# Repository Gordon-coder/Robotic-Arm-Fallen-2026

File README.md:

# Robotic Arm

This is the github repo for the Robotic Arm Project in Hack Club's Fallen 2026.

# Hardware

We have decided to make seperate pcbs for the different parts of the robotic arm to increaase modularity and speed up development. the modules are connected either through a uart line or the ESP-NOW protocol.

PCB for the main arm

Schematic for the main arm

schematic for the camera

# Team Members

<ul>
    <li>
        Gordon Peng
    </li>
    <li>
        Manvith
    </li>
    <li>
        Sarthak Vishwakarma
    </li>
</ul>

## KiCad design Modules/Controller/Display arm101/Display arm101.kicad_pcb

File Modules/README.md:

# Module Development Notes

The mount has 4 4mm holes in a circle with radius 10mm. All modules mounted on the claw mount must use the exact same mounting point.

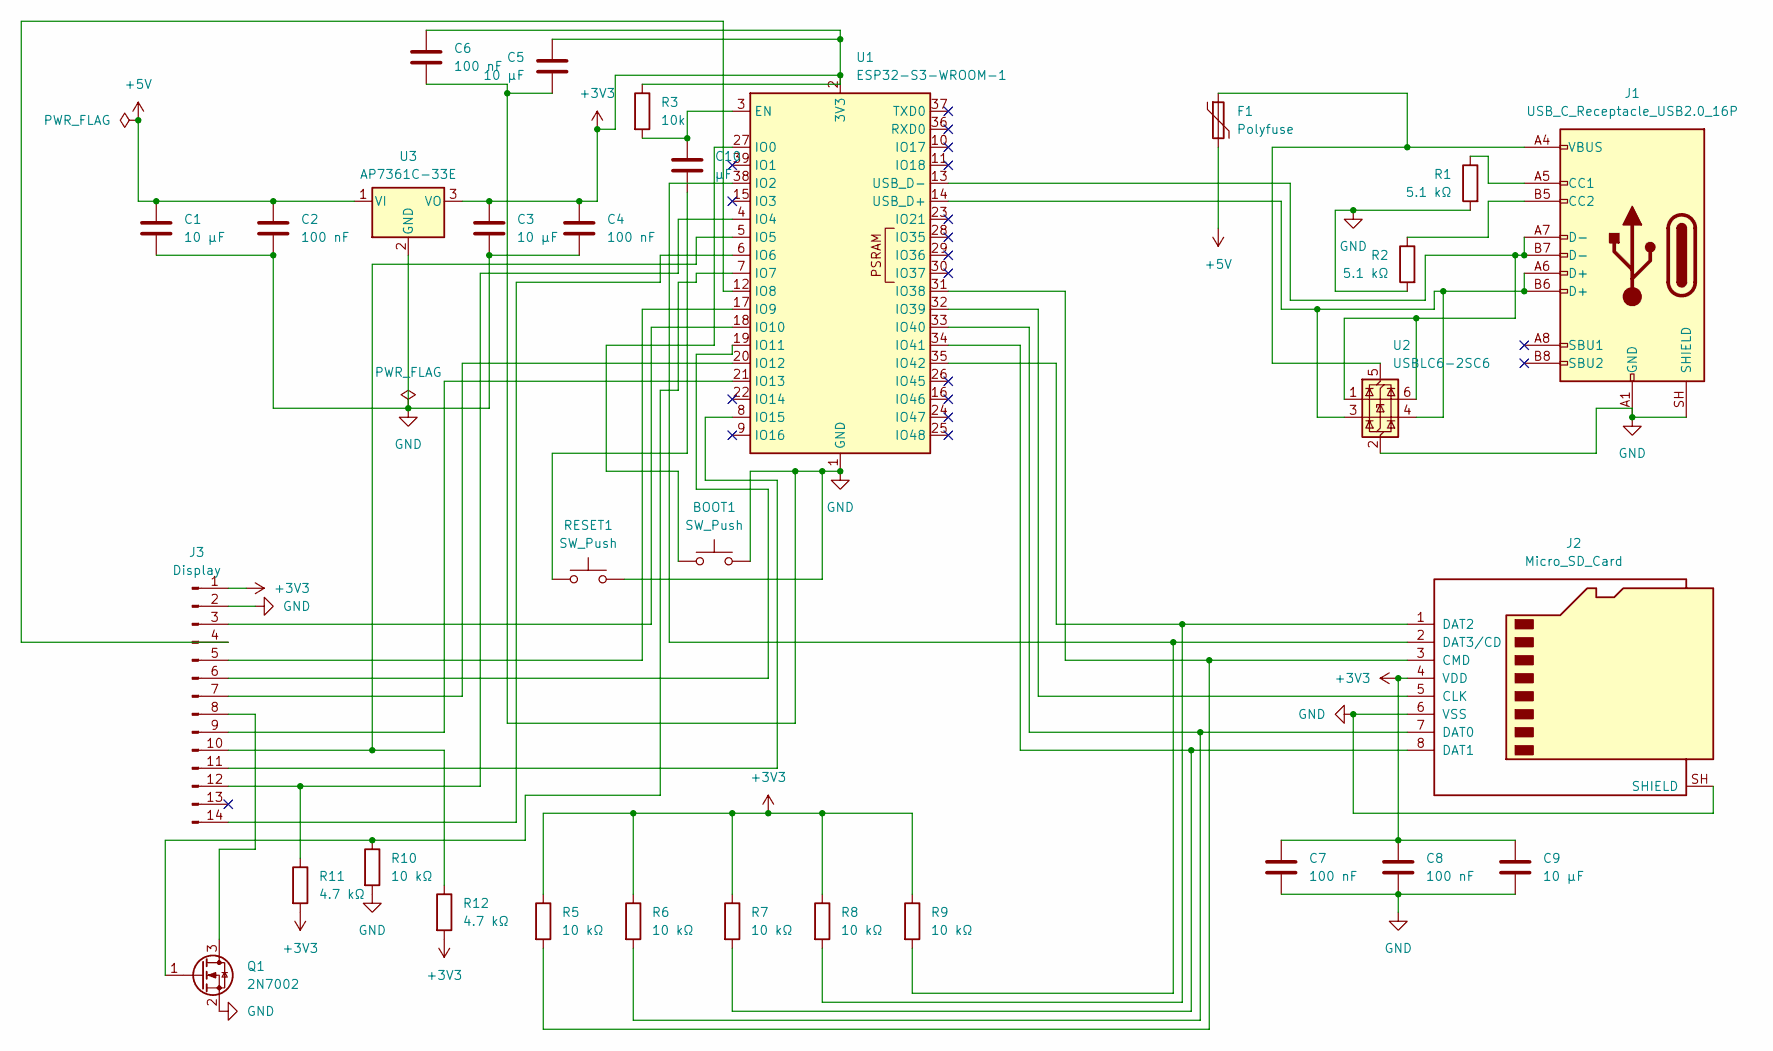
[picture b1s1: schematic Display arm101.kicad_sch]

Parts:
BOOT1: SW_Push; SW_PUSH_6mm
C1, C3, C5, C9: 10 µF; C_0805_2012Metric
C2, C4, C6, C7, C8: 100 nF; C_0805_2012Metric
C10: µF; C_0805_2012Metric
F1: Polyfuse; Fuse_1206_3216Metric
J1: USB_C_Receptacle_USB2.0_16P; USB_C_Receptacle_HRO_TYPE-C-31-M-12
J2: Micro_SD_Card; microSD_HC_Hirose_DM3AT-SF-PEJM5
J3: Display; PinSocket_1x14_P2.54mm_Vertical
Q1: 2N7002; SOT-23
R1, R2: 5.1 kΩ; R_0805_2012Metric
R3: 10k; R_0805_2012Metric
R5, R6, R7, R8, R9, R10: 10 kΩ; R_0805_2012Metric
R11, R12: 4.7 kΩ; R_0805_2012Metric
RESET1: SW_Push; SW_SPST_TL3342
U1: ESP32-S3-WROOM-1
U2: USBLC6-2SC6; SOT-23-6
U3: AP7361C-33E; SOT-223-3_TabPin2

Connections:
+3V3: C3.1, C4.1, C5.1, C6.1, C7.1, C8.1, C9.1, J2.4 (VDD), J3.1, R3.1, R5.1, R6.1, R7.1, R8.1, R9.1, R11.2, R12.2, U1.2 (3V3), U3.3 (VO)
+5V: C1.1, C2.1, F1.2, U3.1 (VI)
GND: BOOT1.2, C1.2, C2.2, C3.2, C4.2, C5.2, C6.2, C7.2, C8.2, C9.2, J1.A1 (GND), J1.A12 (GND), J1.B1 (GND), J1.B12 (GND), J1.SH (SHIELD), J2.6 (VSS), J2.SH (SHIELD), J3.2, Q1.2 (S), R1.2, R2.2, R10.2, RESET1.2, U1.1 (GND), U1.40 (GND), U1.41 (GND), U2.2 (GND), U3.2 (GND)
unnamed: C10.2, RESET1.1
unnamed: J1.A5 (CC1), R1.1
unnamed: J1.B5 (CC2), R2.1
unnamed: J2.5 (CLK), U1.32 (IO39)
unnamed: J2.3 (CMD), R5.2, U1.31 (IO38)
unnamed: J2.7 (DAT0), R6.2, U1.33 (IO40)
unnamed: J2.8 (DAT1), R7.2, U1.34 (IO41)
unnamed: J2.1 (DAT2), R8.2, U1.35 (IO42)
unnamed: J2.2 (DAT3/CD), R9.2, U1.38 (IO2)
unnamed: J3.3, U1.18 (IO10)
unnamed: J3.4, U1.12 (IO8)
unnamed: J3.5, U1.17 (IO9)
unnamed: J3.6, U1.19 (IO11)
unnamed: J3.7, U1.20 (IO12)
unnamed: J3.8, Q1.3 (D)
unnamed: J3.9, U1.21 (IO13)
unnamed: J3.10, R12.1, U1.5 (IO5)
unnamed: J3.11, U1.8 (IO15)
unnamed: J3.12, R11.1, U1.4 (IO4)
unnamed: J3.14, U1.6 (IO6)
unnamed: Q1.1 (G), R10.1, U1.7 (IO7)
unnamed: C10.1, R3.2, U1.3 (EN)
unnamed: BOOT1.1, U1.27 (IO0)
unnamed: J1.A6 (D+), J1.B6 (D+), U1.14 (USB_D+), U2.3 (I/O2), U2.4 (I/O2)
unnamed: J1.A7 (D-), J1.B7 (D-), U1.13 (USB_D-), U2.1 (I/O1), U2.6 (I/O1)
unnamed: F1.1, J1.A4 (VBUS), J1.A9 (VBUS), J1.B4 (VBUS), J1.B9 (VBUS), U2.5 (VBUS)

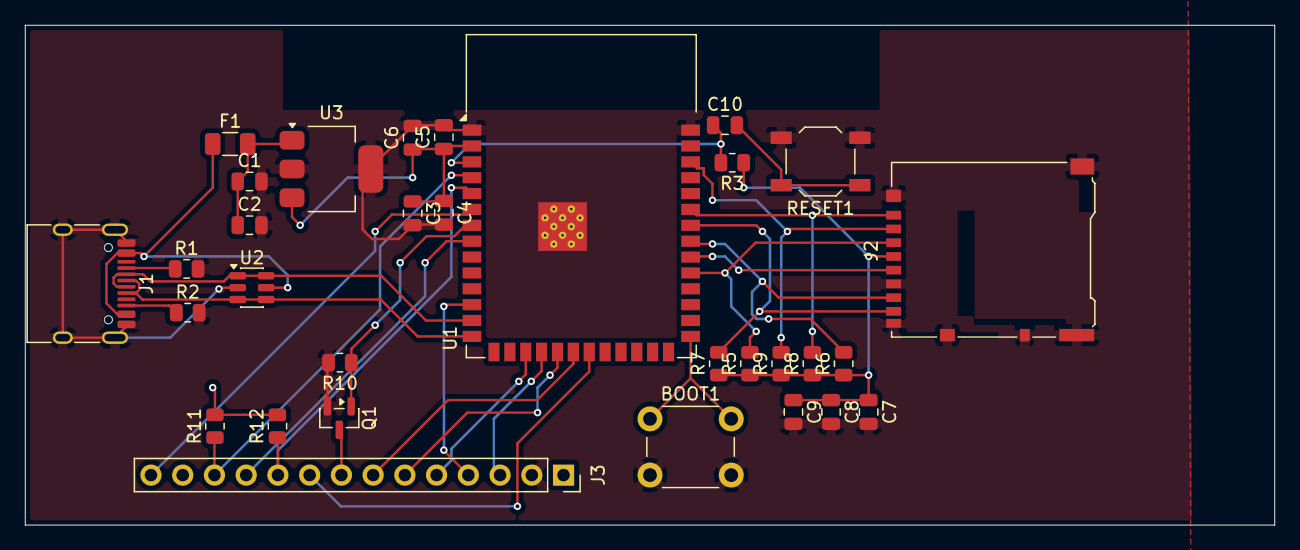
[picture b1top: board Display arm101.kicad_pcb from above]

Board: 2 copper layers, 100.0 x 40.0 mm, 31 parts (0 on the bottom side), 29 nets.

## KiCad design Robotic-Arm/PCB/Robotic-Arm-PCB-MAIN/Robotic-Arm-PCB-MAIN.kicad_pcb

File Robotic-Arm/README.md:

# Model Specifications

All of the models use a m3\*10 screw and a m3\*4\*4 heatset insert. The servo horns are directly screwed into the plastic using wood screws as well for now.

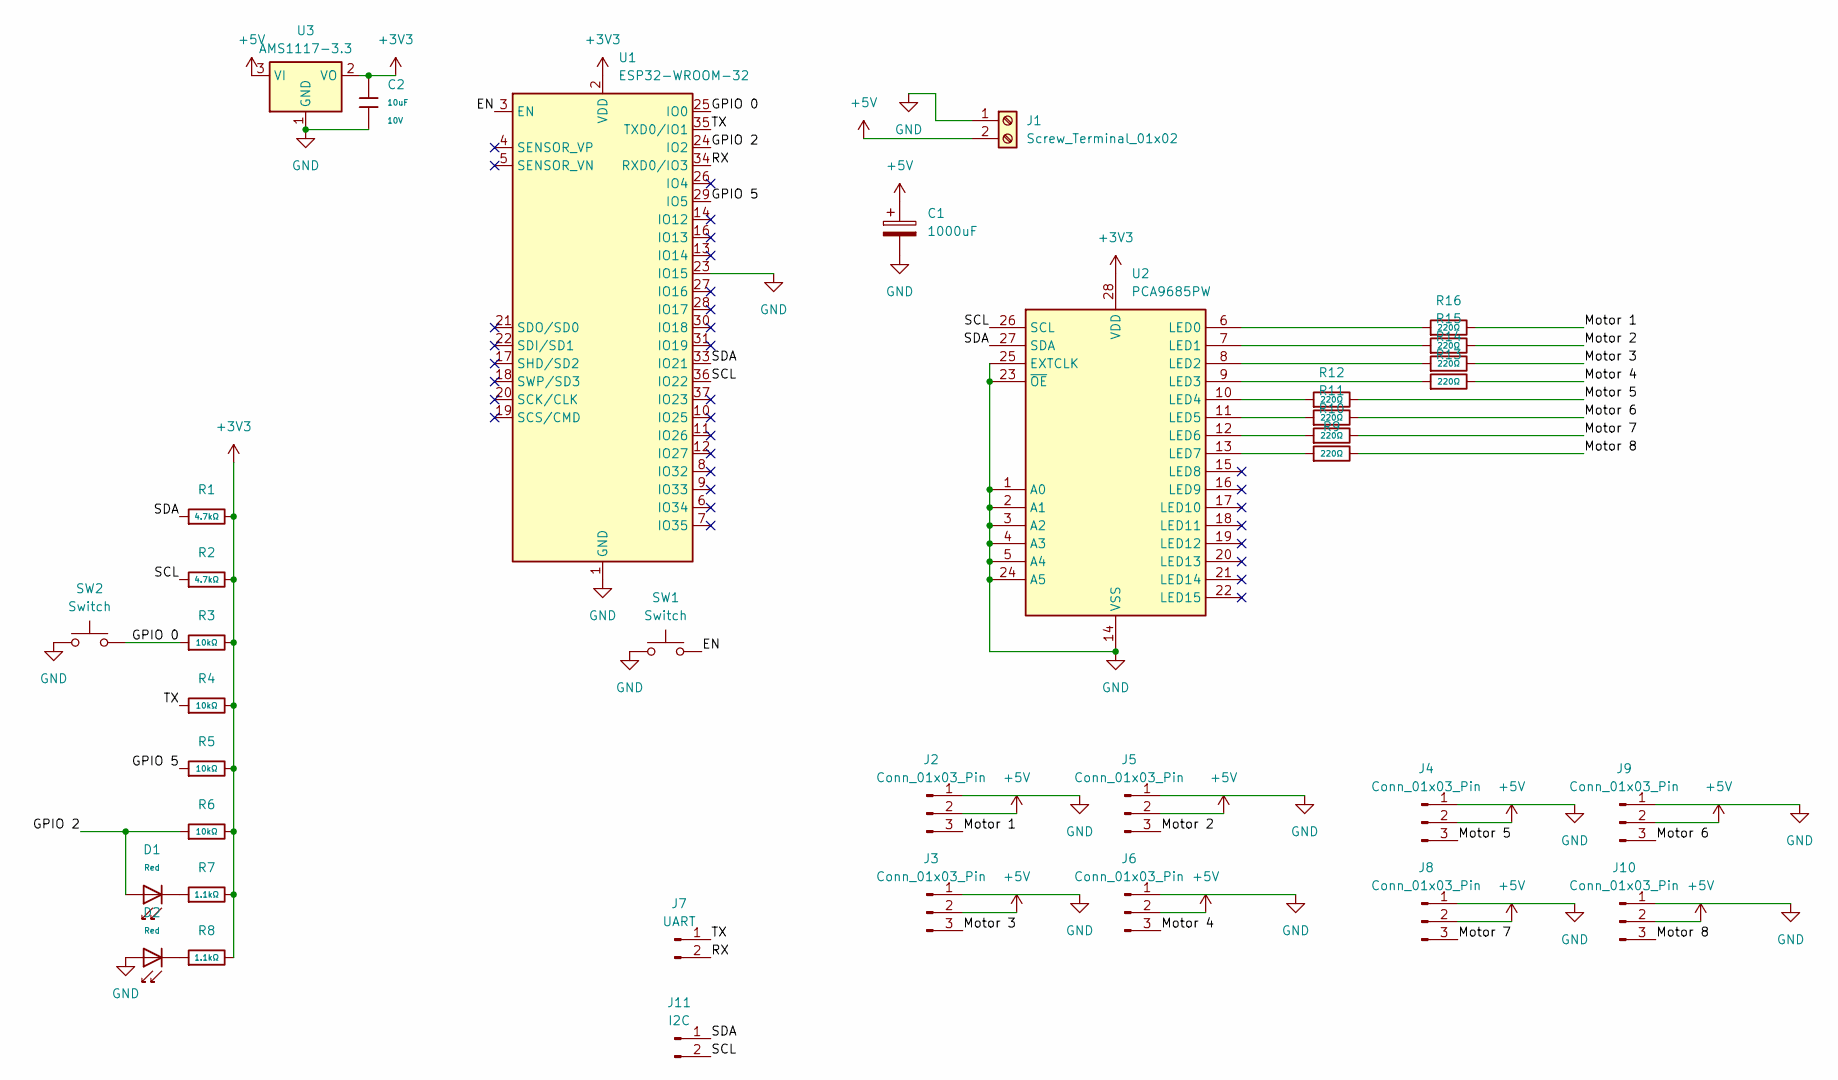
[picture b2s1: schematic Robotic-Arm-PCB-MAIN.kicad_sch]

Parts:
C1: 1000uF; CP_Radial_D8.0mm_P3.50mm
C2: 10uF; C_0603; Voltage Rated 10V; Tolerance ±10%; Part CL10A106KP8NNNC; LCSC C19702
D1, D2: Red; D_0603; Part KT-0603R; LCSC C2286
J1: Screw_Terminal_01x02; TerminalBlock_MaiXu_MX126-5.0-02P_1x02_P5.00mm
J2, J3, J4, J5, J6, J8, J9, J10: Conn_01x03_Pin; PinHeader_1x03_P2.54mm_Vertical
J7: UART; PinHeader_1x02_P2.54mm_Vertical
J11: I2C; PinHeader_1x02_P2.54mm_Vertical
R1, R2: 4.7kΩ; R_0603; Overload Voltage (Max) 75V; Tolerance ±1%; Part 0603WAF4701T5E; LCSC C23162
R3, R4, R5, R6: 10kΩ; R_0603; Overload Voltage (Max) 75V; Tolerance ±1%; Part 0603WAF1002T5E; LCSC C25804
R7, R8: 1.1kΩ; R_0603; Overload Voltage (Max) 75V; Tolerance ±1%; Part 0603WAF1101T5E; LCSC C22764
R9, R10, R11, R12, R13, R14, R15, R16: 220Ω; R_0603; Overload Voltage (Max) 75V; Tolerance ±1%; Part 0603WAF2200T5E; LCSC C22962
SW1, SW2: Switch; SW_Push_1P1T_NO_E-Switch_TL3301NxxxxxG
U1: ESP32-WROOM-32
U2: PCA9685PW; TSSOP-28_4.4x9.7mm_P0.65mm
U3: AMS1117-3.3; SOT-223-3_TabPin2

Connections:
+3V3: C2.1, R1.2, R2.2, R3.2, R4.2, R5.2, R6.2, R7.2, R8.2, U1.2 (VDD), U2.28 (VDD), U3.2 (VO)
+5V: C1.1, J1.2, J2.2, J3.2, J4.2, J5.2, J6.2, J8.2, J9.2, J10.2, U3.3 (VI)
/EN: SW1.2, U1.3 (EN)
/GPIO 0: R3.1, SW2.2, U1.25 (IO0)
/GPIO 2: D1.2, R6.1, U1.24 (IO2)
/GPIO 5: R5.1, U1.29 (IO5)
/Motor 1: J2.3, R16.2
/Motor 2: J5.3, R15.2
/Motor 3: J3.3, R14.2
/Motor 4: J6.3, R13.2
/Motor 5: J4.3, R12.2
/Motor 6: J9.3, R11.2
/Motor 7: J8.3, R10.2
/Motor 8: J10.3, R9.2
/RX: J7.2, U1.34 (RXD0/IO3)
/SCL: J11.2, R2.1, U1.36 (IO22), U2.26 (SCL)
/SDA: J11.1, R1.1, U1.33 (IO21), U2.27 (SDA)
/TX: J7.1, R4.1, U1.35 (TXD0/IO1)
GND: C1.2, C2.2, D2.2, J1.1, J2.1, J3.1, J4.1, J5.1, J6.1, J8.1, J9.1, J10.1, SW1.1, SW2.1, U1.1 (GND), U1.15 (GND), U1.23 (IO15), U1.38 (GND), U1.39 (GND), U2.1 (A0), U2.2 (A1), U2.3 (A2), U2.4 (A3), U2.5 (A4), U2.14 (VSS), U2.23 (~OE), U2.24 (A5), U2.25 (EXTCLK), U3.1 (GND)
unnamed: D1.1, R7.1
unnamed: D2.1, R8.1
unnamed: R16.1, U2.6 (LED0)
unnamed: R15.1, U2.7 (LED1)
unnamed: R14.1, U2.8 (LED2)
unnamed: R13.1, U2.9 (LED3)
unnamed: R12.1, U2.10 (LED4)
unnamed: R11.1, U2.11 (LED5)
unnamed: R10.1, U2.12 (LED6)
unnamed: R9.1, U2.13 (LED7)

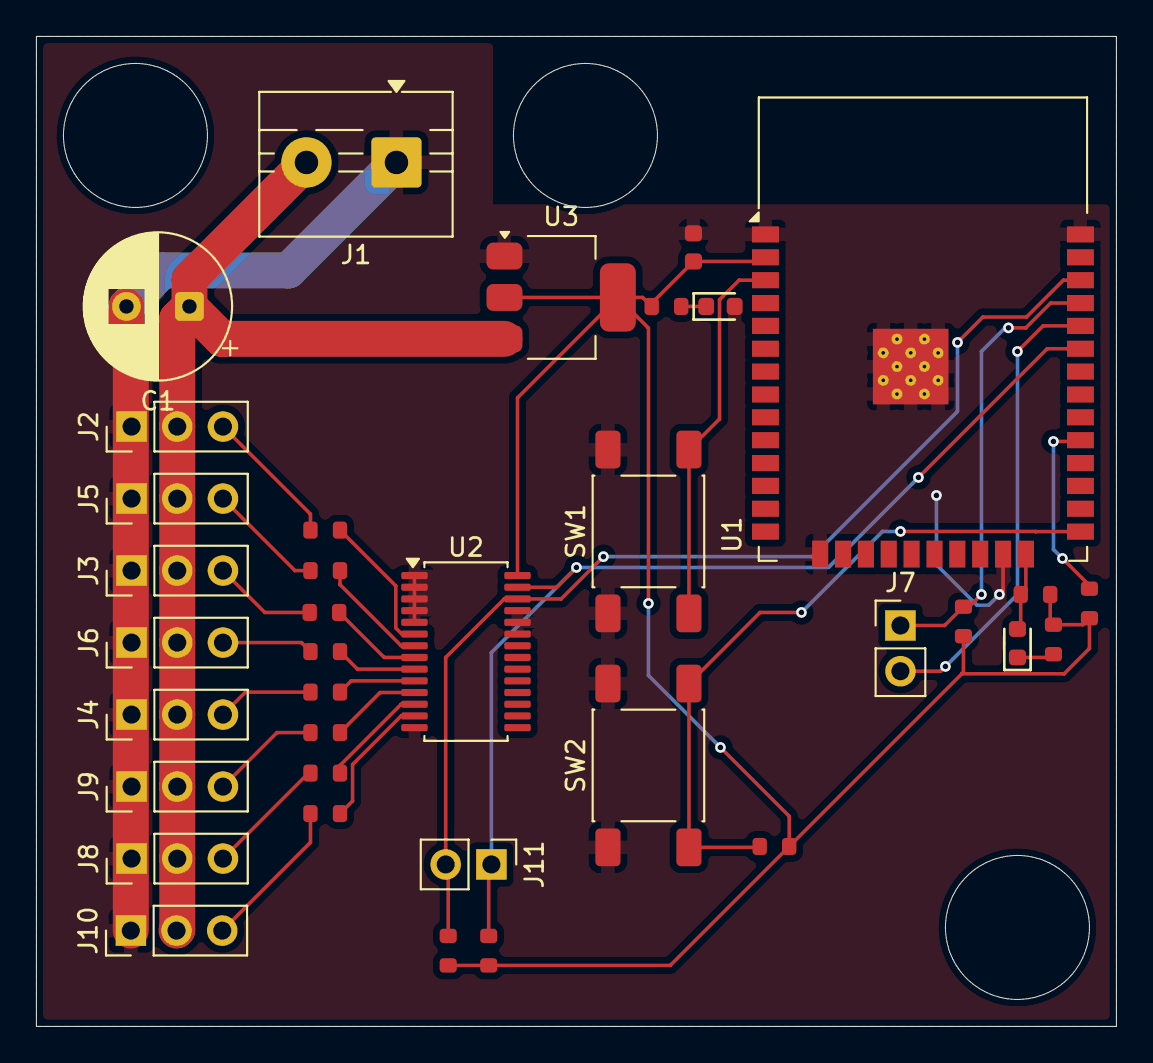
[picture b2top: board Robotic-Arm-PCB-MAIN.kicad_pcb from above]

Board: 2 copper layers, 60.0 x 55.0 mm, 36 parts (0 on the bottom side), 29 nets.

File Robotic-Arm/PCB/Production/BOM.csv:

"Value","Reference","Qty","Exclude from BOM","Footprint","Datasheet","Capacitance"
"Switch","SW1,SW2","2","","Button_Switch_SMD:SW_Push_1P1T_NO_E-Switch_TL3301NxxxxxG","",""
"Red","D1,D2","2","","PCM_JLCPCB:D_0603","https://www.lcsc.com/datasheet/lcsc_datasheet_1810231112_Hub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",""
"PCA9685PW","U2","1","","Package_SO:TSSOP-28_4.4x9.7mm_P0.65mm","http://www.nxp.com/docs/en/data-sheet/PCA9685.pdf",""
"ESP32-WROOM-32","U1","1","","RF_Module:ESP32-WROOM-32","https://www.espressif.com/sites/default/files/documentation/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",""
"AMS1117-3.3","U3","1","","Package_TO_SOT_SMD:SOT-223-3_TabPin2","http://www.advanced-monolithic.com/pdf/ds1117.pdf",""
"220Ω","R9,R10,R11,R12,R13,R14,R15,R16","8","","PCM_JLCPCB:R_0603","https://www.lcsc.com/datasheet/lcsc_datasheet_2206010130_UNI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",""
"10kΩ","R3,R4,R5,R6","4","","PCM_JLCPCB:R_0603","https://www.lcsc.com/datasheet/lcsc_datasheet_2206010045_UNI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",""
"4.7kΩ","R1,R2","2","","PCM_JLCPCB:R_0603","https://www.lcsc.com/datasheet/lcsc_datasheet_2206010116_UNI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",""
"1.1kΩ","R7,R8","2","","PCM_JLCPCB:R_0603","https://www.lcsc.com/datasheet/lcsc_datasheet_2206010130_UNI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",""
"1000uF","C1","1","","Capacitor_THT:CP_Radial_D8.0mm_P3.50mm","",""
"10uF","C2","1","","PCM_JLCPCB:C_0603","https://www.lcsc.com/datasheet/lcsc_datasheet_2304140030_Sam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","10uF"
